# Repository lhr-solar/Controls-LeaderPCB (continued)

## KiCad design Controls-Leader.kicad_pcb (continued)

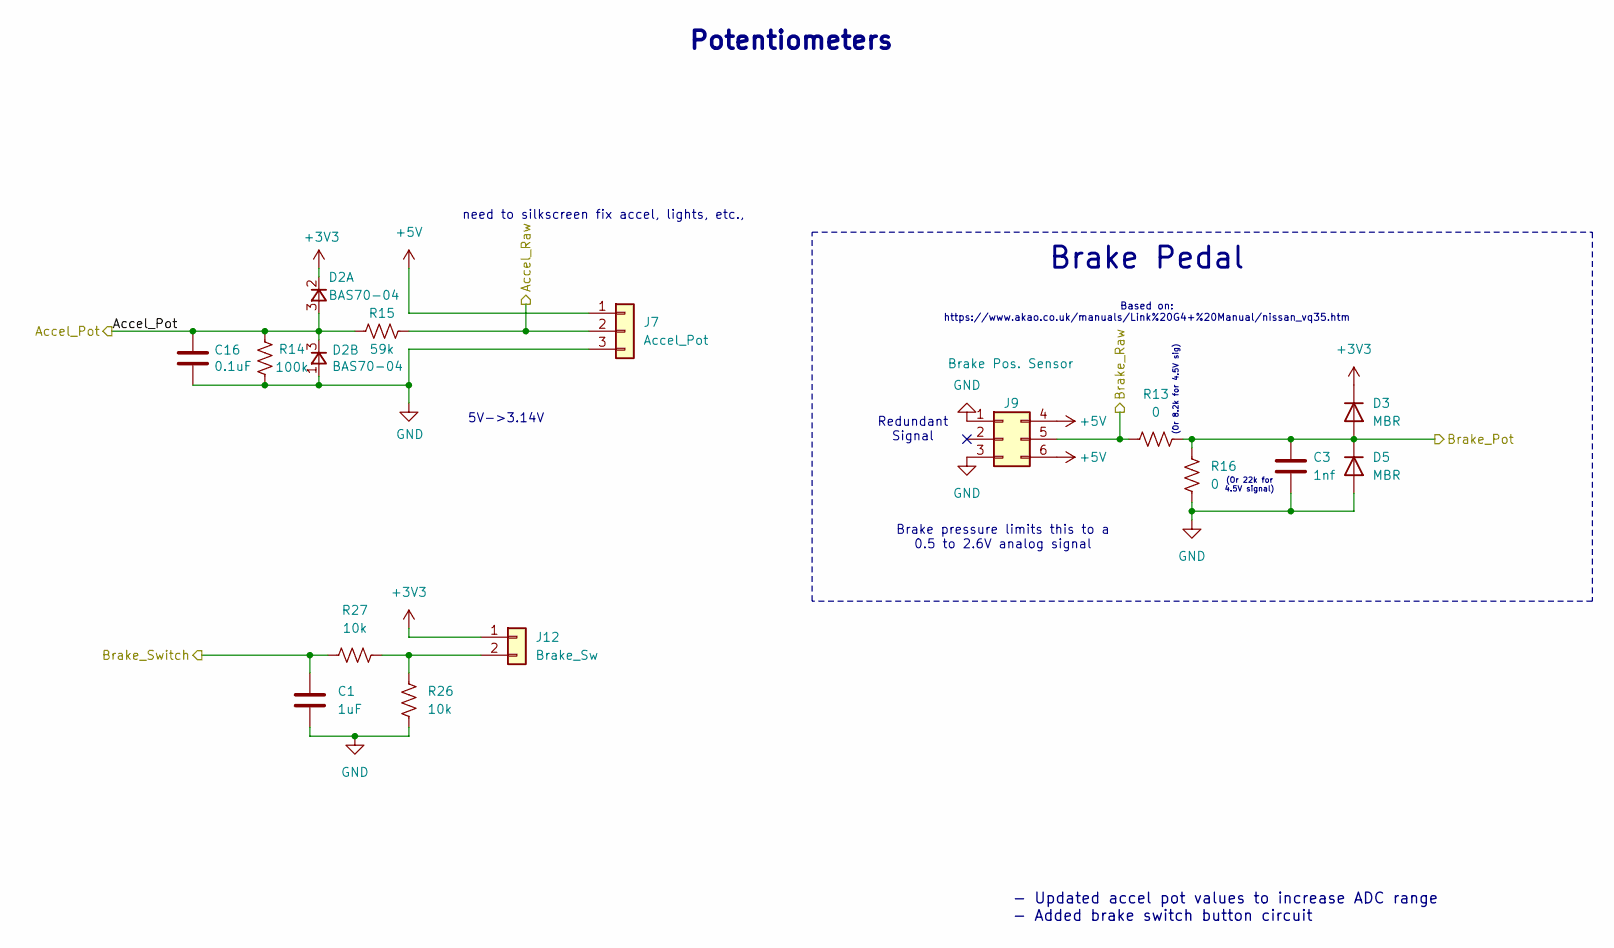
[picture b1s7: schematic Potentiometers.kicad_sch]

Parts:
C1: 1uF; C_0805_2012Metric; JLCPCB# C28323
C3: 1nf; C_0805_2012Metric; JLCPCB# C1791
C16: 0.1uF; C_0805_2012Metric; Mouser Part Number 80-C0805C104M5R
D2: BAS70-04; SOT-23; Mouser Part Number 652-CDSOT23-T24CAN
D3, D5: MBR; D_0805_2012Metric; JLCPCB# C23848
J7: Accel_Pot; Molex_Micro-Fit_3.0_43650-0315_1x03_P3.00mm_Vertical
J9: Brake Pos. Sensor; Molex_Micro-Fit_3.0_43045-0612_2x03_P3.00mm_Vertical
J12: Brake_Sw; Molex_Micro-Fit_3.0_43650-0215_1x02_P3.00mm_Vertical
R13, R16: 0; R_0805_2012Metric; JLCPCB# C17477
R14: 100k; R_0805_2012Metric; Mouser Part Number 71-CRCW0805100KFKEAC
R15: 59k; R_0805_2012Metric; Mouser Part Number 71-CRCW08054K99FKEAC
R26, R27: 10k; R_0805_2012Metric; Mouser Part Number 71-CRCW080510K0FKEAC

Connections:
+3V3: D2.2, D3.1 (K), D3.K, J12.1; also elsewhere on the board
+5V: J7.1, J9.4, J9.6; also elsewhere on the board
/Accel_Pot: C16.1, D2.3, R14.1, R15.2; also elsewhere on the board
/Accel_Raw: J7.2, R15.1; also elsewhere on the board
/Brake_Pot: C3.2, D3.2 (A), D3.A, D5.1 (K), D5.K, R13.1, R16.1; also elsewhere on the board
/Brake_Raw: J9.5, R13.2; also elsewhere on the board
/Brake_SW: C1.1, R27.1; also elsewhere on the board
GND: C1.2, C3.1, C16.2, D2.1, D5.2 (A), D5.A, J7.3, J9.1, J9.3, R14.2, R16.2, R26.2; also elsewhere on the board
unnamed: J12.2, R26.1, R27.2

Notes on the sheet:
(Or 22k for 4.5V signal)
Potentiometers
- Updated accel pot values to increase ADC range - Added brake switch button circuit
Redundant Signal
need to silkscreen fix accel, lights, etc.,
Brake pressure limits this to a 0.5 to 2.6V analog signal
5V->3.14V
(Or 8.2k for 4.5V sig)
Based on: https://www.akao.co.uk/manuals/Link%20G4+%20Manual/nissan_vq35.htm
Brake Pedal

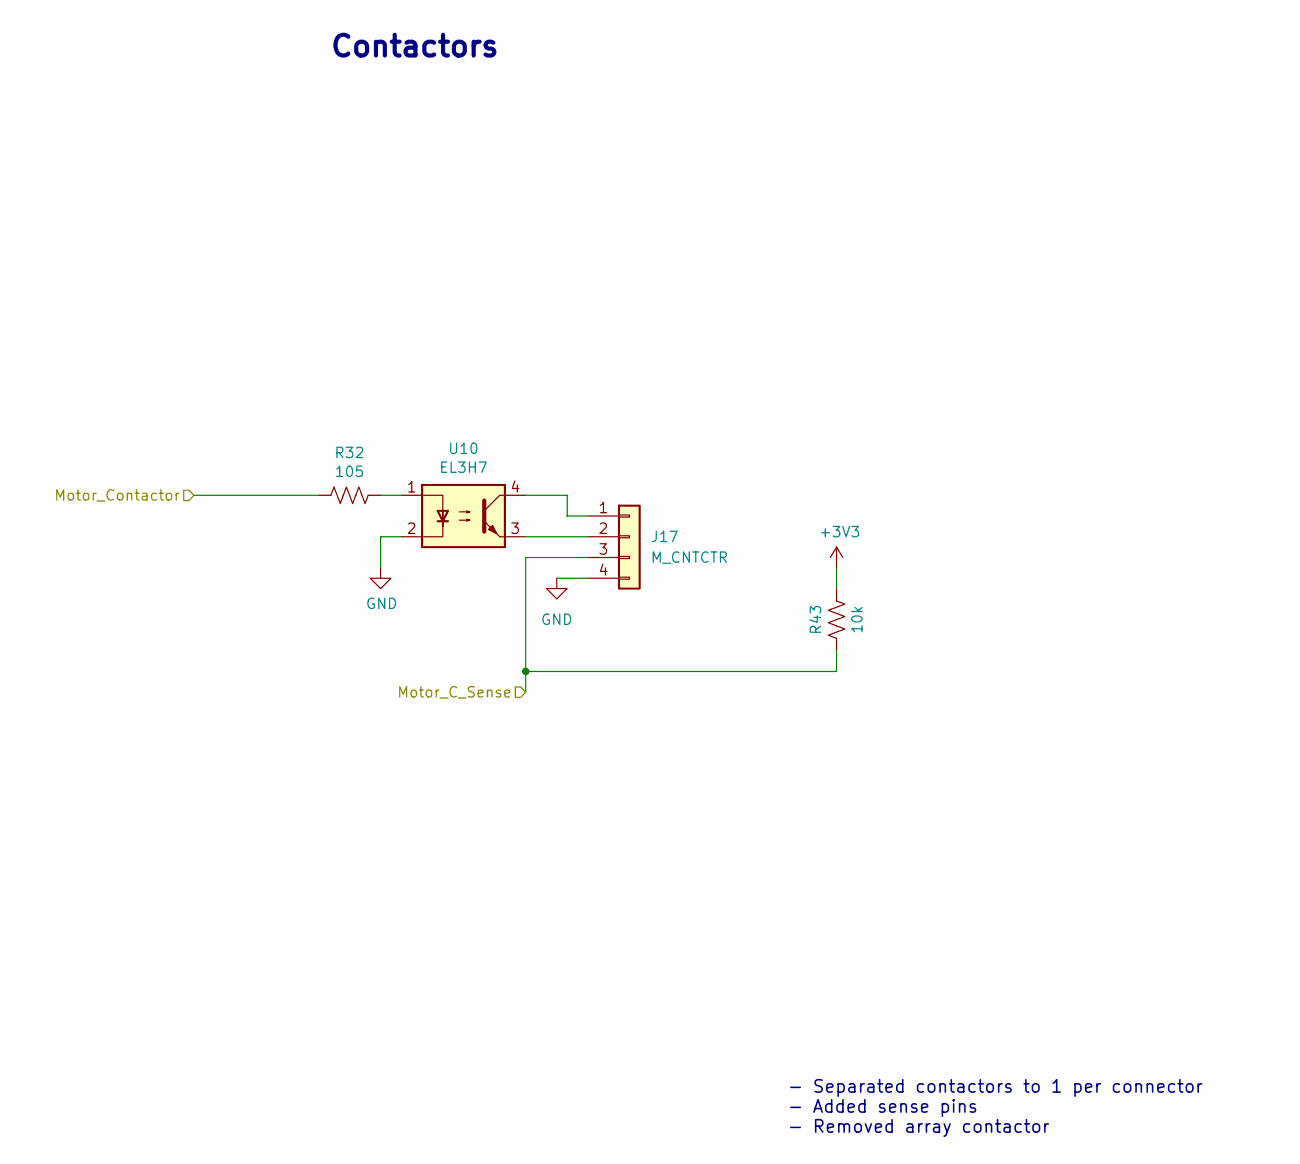
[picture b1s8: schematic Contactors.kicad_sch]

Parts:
J17: M_CNTCTR; Molex_Micro-Fit_3.0_43650-0415_1x04_P3.00mm_Vertical
R32: 105; R_0805_2012Metric; Mouser Part Number 71-CRCW0805105RFKEA
R43: 10k; R_0805_2012Metric; Mouser Part Number 71-CRCW080510K0FKEAC
U10: EL3H7; SSOP-4_4.4x2.6mm_P1.27mm; Mouser Part Number 638-EL3H7DTAVG

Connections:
+3V3: R43.1; also elsewhere on the board
/Motor_C_Sense: J17.3, R43.2; also elsewhere on the board
/Motor_Contactor: R32.2; also elsewhere on the board
GND: J17.4, U10.2; also elsewhere on the board
unnamed: J17.1, U10.4
unnamed: J17.2, U10.3
unnamed: R32.1, U10.1

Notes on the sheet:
Contactors
- Separated contactors to 1 per connector - Added sense pins - Removed array contactor

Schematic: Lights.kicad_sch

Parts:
BRAKELIGHT1: EXTERNAL_BRAKELIGHT; Molex_Micro-Fit_3.0_43650-0215_1x02_P3.00mm_Vertical; JLCPCB# C293740
LOGO4: UTSVT Logo; UTSVT_Logo_Symbol
L_BLINK_EXT1: EXTERNAL_LEFTBLINK; Molex_Micro-Fit_3.0_43650-0215_1x02_P3.00mm_Vertical; JLCPCB# C293740
Q1, Q3, Q4: IRLML0030; SOT-23; JLCPCB# C67272
R6, R12, R41: 510; R_0805_2012Metric; Mouser Part Number 71-CRCW0805510RFKEAC
R11, R45, R46: 100k; R_0805_2012Metric; Mouser Part Number 71-CRCW0805100KFKEAC
R_BLINK_EXT1: EXTERNAL_RIGHTBLINK; Molex_Micro-Fit_3.0_43650-0215_1x02_P3.00mm_Vertical; JLCPCB# C293740
TP7: RIGHT_BLINK; TestPoint_Keystone_5005-5009_Compact
TP8: LEFT_BLINK; TestPoint_Keystone_5005-5009_Compact
U3, U16, U20: EL3H7; SSOP-4_4.4x2.6mm_P1.27mm; Mouser Part Number 638-EL3H7DTAVG

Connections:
/Brake_Light: R6.1; also elsewhere on the board
/Left_Blink: R41.1, TP8.1; also elsewhere on the board
/Right_Blink: R12.1, TP7.1; also elsewhere on the board
GND: U3.2, U16.2, U20.2; also elsewhere on the board
GNDPWR: Q1.2 (S), Q3.2 (S), Q4.2 (S), R11.2, R45.2, R46.2; also elsewhere on the board
Lights_12V: BRAKELIGHT1.1, L_BLINK_EXT1.1, R_BLINK_EXT1.1, U3.4, U16.4, U20.4; also elsewhere on the board
unnamed: BRAKELIGHT1.2, Q1.3 (D)
unnamed: L_BLINK_EXT1.2, Q4.3 (D)
unnamed: Q1.1 (G), R11.1, U3.3
unnamed: Q3.3 (D), R_BLINK_EXT1.2
unnamed: Q3.1 (G), R45.1, U16.3
unnamed: Q4.1 (G), R46.1, U20.3
unnamed: R6.2, U3.1
unnamed: R12.2, U16.1
unnamed: R41.2, U20.1

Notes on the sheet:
Lights Drivers
- Replaced lights drivers/circuits - Replaced 555 timer with blinking gpio that passes through to drivers when dashboard Left/Right 3-pos switch is toggled - Intended to connect to breakout boards that split out the necessary number of lights

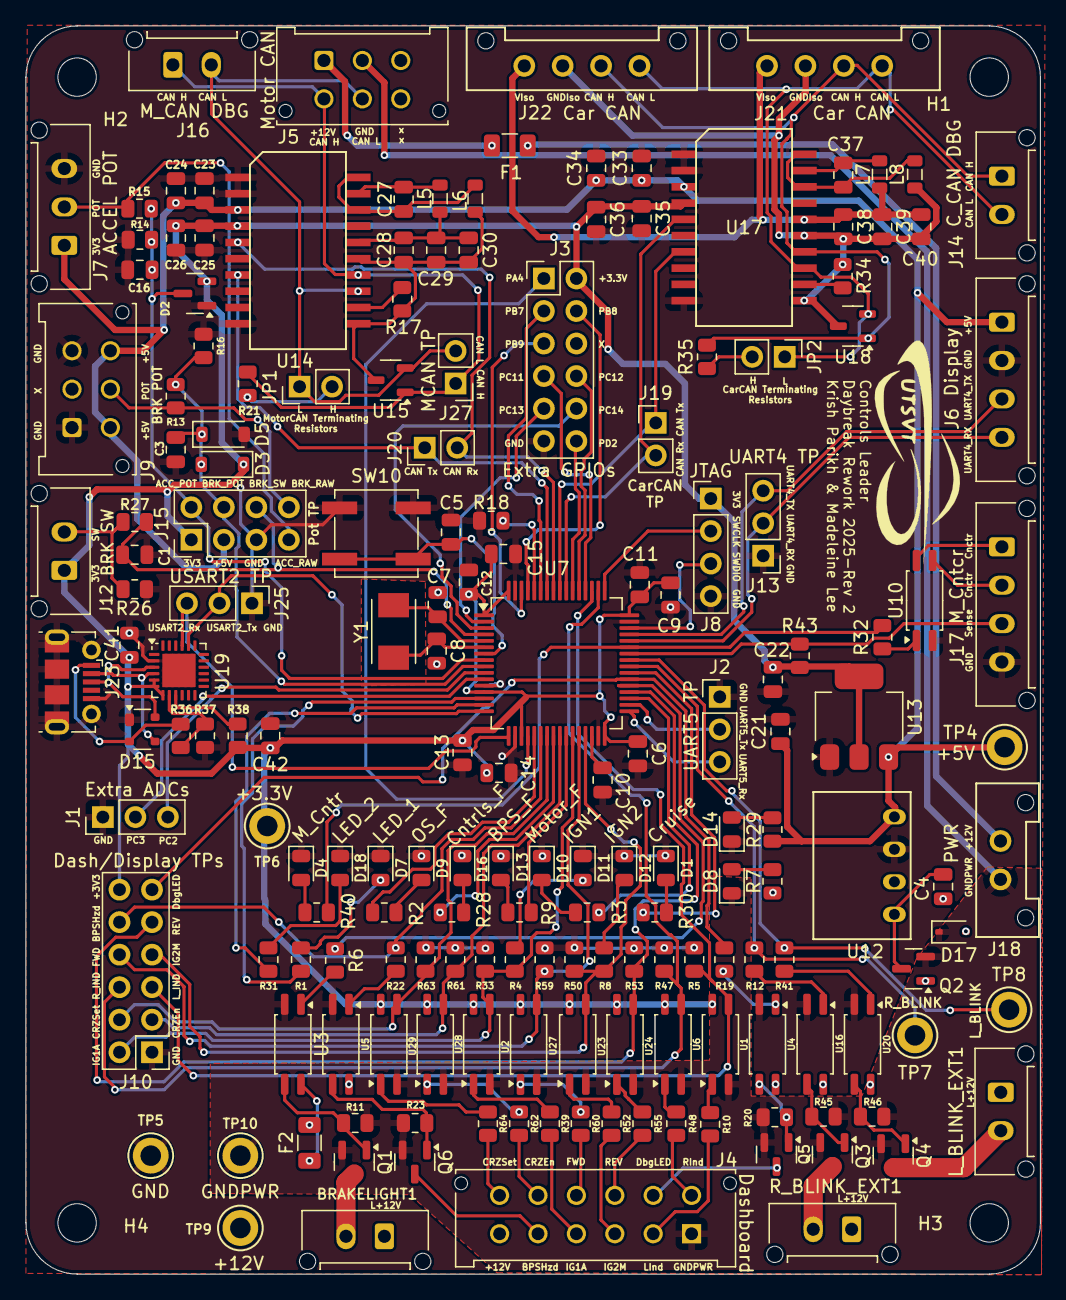
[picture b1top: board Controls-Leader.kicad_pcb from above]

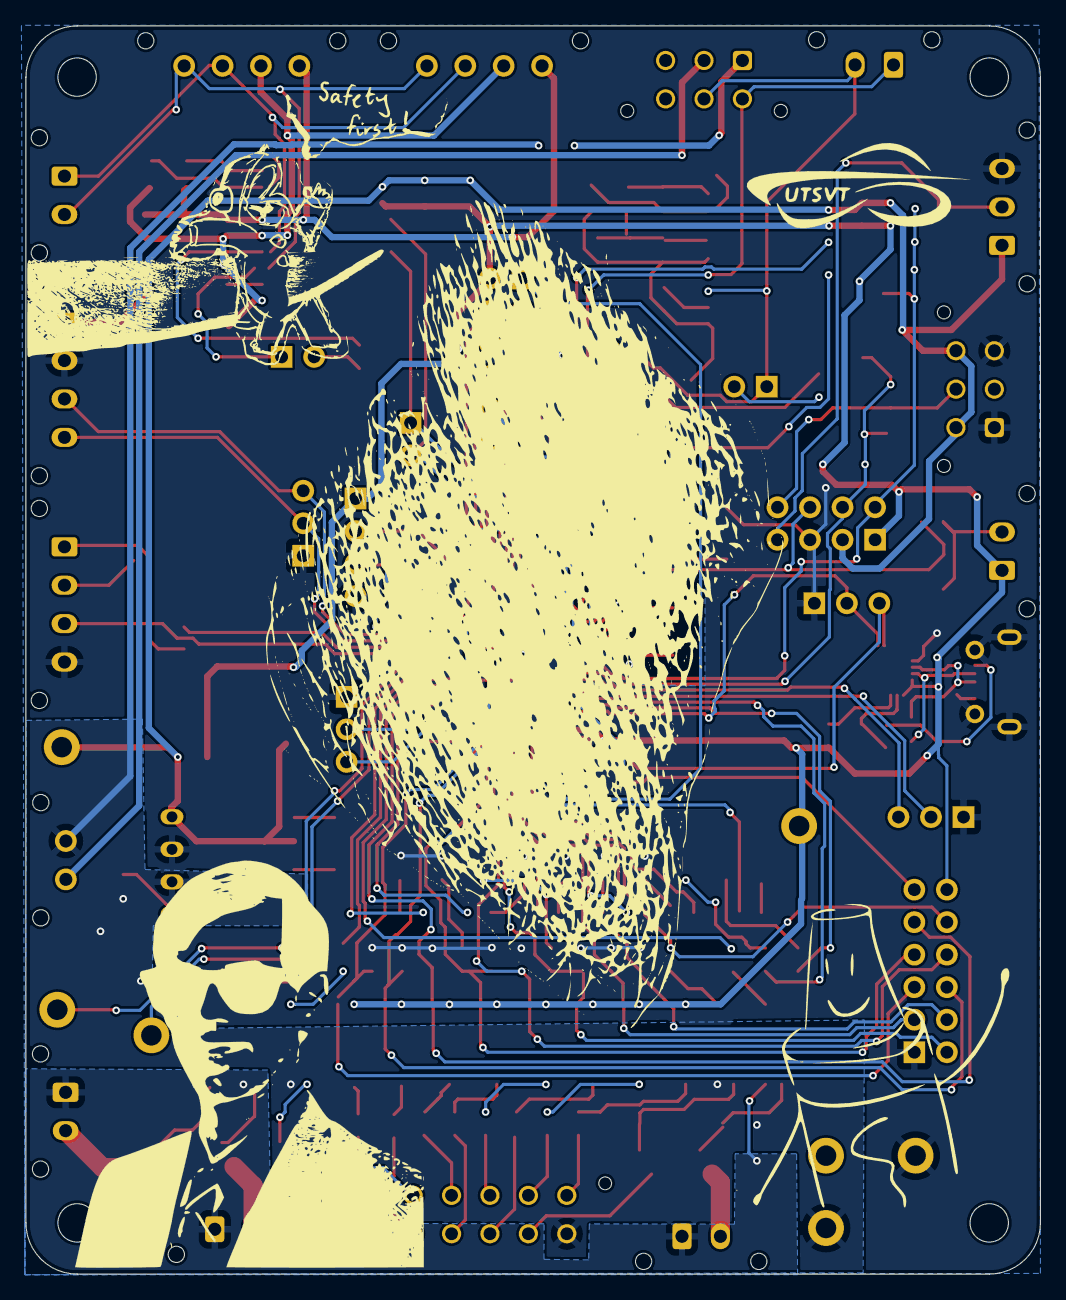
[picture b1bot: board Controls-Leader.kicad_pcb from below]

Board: 2 copper layers, 79.2 x 97.5 mm, 185 parts (2 on the bottom side), 131 nets.

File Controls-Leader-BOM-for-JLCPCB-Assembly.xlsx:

Comment | Designator | Footprint | JLCPCB#
1.8k | L5 | Inductor_SMD:L_0805_2012Metric | C394483
1.8k | L6 | Inductor_SMD:L_0805_2012Metric | C394483
1.8k | L7 | Inductor_SMD:L_0805_2012Metric | C394483
1.8k | L8 | Inductor_SMD:L_0805_2012Metric | C394483
CP2102N-A02-GQFN24 | U19 | Package_DFN_QFN:QFN-24-1EP_4x4mm_P0.5mm_EP2.6x2.6mm | C969151
698 | R1 | Resistor_SMD:R_0805_2012Metric | C101843
698 | R2 | Resistor_SMD:R_0805_2012Metric | C101843
698 | R3 | Resistor_SMD:R_0805_2012Metric | C101843
698 | R4 | Resistor_SMD:R_0805_2012Metric | C101843
698 | R8 | Resistor_SMD:R_0805_2012Metric | C101843
698 | R9 | Resistor_SMD:R_0805_2012Metric | C101843
698 | R28 | Resistor_SMD:R_0805_2012Metric | C101843
698 | R30 | Resistor_SMD:R_0805_2012Metric | C101843
698 | R31 | Resistor_SMD:R_0805_2012Metric | C101843
698 | R40 | Resistor_SMD:R_0805_2012Metric | C101843
Crystal | Y1 | Crystal:Crystal_SMD_TXC_7A-2Pin_5x3.2mm | C115962
100k | R11 | Resistor_SMD:R_0805_2012Metric | C149504
100k | R14 | Resistor_SMD:R_0805_2012Metric | C149504
100k | R20 | Resistor_SMD:R_0805_2012Metric | C149504
100k | R23 | Resistor_SMD:R_0805_2012Metric | C149504
100k | R45 | Resistor_SMD:R_0805_2012Metric | C149504
100k | R46 | Resistor_SMD:R_0805_2012Metric | C149504
10uF | C4 | Capacitor_SMD:C_0805_2012Metric | C15850
10uF | C21 | Capacitor_SMD:C_0805_2012Metric | C15850
10uF | C22 | Capacitor_SMD:C_0805_2012Metric | C15850
10uF | C23 | Capacitor_SMD:C_0805_2012Metric | C15850
10uF | C28 | Capacitor_SMD:C_0805_2012Metric | C15850
10uF | C33 | Capacitor_SMD:C_0805_2012Metric | C15850
10uF | C38 | Capacitor_SMD:C_0805_2012Metric | C15850
0.01uF | C26 | Capacitor_SMD:C_0805_2012Metric | C1710
0.01uF | C30 | Capacitor_SMD:C_0805_2012Metric | C1710
0.01uF | C36 | Capacitor_SMD:C_0805_2012Metric | C1710
0.01uF | C40 | Capacitor_SMD:C_0805_2012Metric | C1710
10k | R18 | Resistor_SMD:R_0805_2012Metric | C17414
10k | R26 | Resistor_SMD:R_0805_2012Metric | C17414
10k | R27 | Resistor_SMD:R_0805_2012Metric | C17414
10k | R43 | Resistor_SMD:R_0805_2012Metric | C17414
120 | R21 | Resistor_SMD:R_0805_2012Metric | C17437
105 | R32 | Resistor_SMD:R_0805_2012Metric | C17437
120 | R35 | Resistor_SMD:R_0805_2012Metric | C17437
0 | R13 | Resistor_SMD:R_0805_2012Metric | C17477
0 | R16 | Resistor_SMD:R_0805_2012Metric | C17477
0 | R17 | Resistor_SMD:R_0805_2012Metric | C17477
0 | R34 | Resistor_SMD:R_0805_2012Metric | C17477
1k | R38 | Resistor_SMD:R_0805_2012Metric | C17513
22.1k | R36 | Resistor_SMD:R_0805_2012Metric | C17560
2k | R10 | Resistor_SMD:R_0805_2012Metric | C17604
2k | R39 | Resistor_SMD:R_0805_2012Metric | C17604
2k | R48 | Resistor_SMD:R_0805_2012Metric | C17604
2k | R52 | Resistor_SMD:R_0805_2012Metric | C17604
2k | R55 | Resistor_SMD:R_0805_2012Metric | C17604
2k | R60 | Resistor_SMD:R_0805_2012Metric | C17604
2k | R62 | Resistor_SMD:R_0805_2012Metric | C17604
2k | R64 | Resistor_SMD:R_0805_2012Metric | C17604
47.5k | R37 | Resistor_SMD:R_0805_2012Metric | C17713
510 | R6 | Resistor_SMD:R_0805_2012Metric | C17734
510 | R12 | Resistor_SMD:R_0805_2012Metric | C17734
510 | R19 | Resistor_SMD:R_0805_2012Metric | C17734
510 | R22 | Resistor_SMD:R_0805_2012Metric | C17734
510 | R41 | Resistor_SMD:R_0805_2012Metric | C17734
59k | R15 | Resistor_SMD:R_0805_2012Metric | C17763
4.7uF | C10 | Capacitor_SMD:C_0805_2012Metric | C1779
4.7uF | C13 | Capacitor_SMD:C_0805_2012Metric | C1779
4.7uF | C41 | Capacitor_SMD:C_0805_2012Metric | C1779
1nf | C3 | Capacitor_SMD:C_0805_2012Metric | C1791
12pF | C7 | Capacitor_SMD:C_0805_2012Metric | C1792
12pF | C8 | Capacitor_SMD:C_0805_2012Metric | C1792
Fuse | F1 | Fuse:Fuse_1206_3216Metric | C206967
Fuse | F2 | Fuse:Fuse_1206_3216Metric | C206970
MBR | D3 | Diode_SMD:D_0805_2012Metric | C23848
MBR | D5 | Diode_SMD:D_0805_2012Metric | C23848
NCP1117-3.3_SOT223 | U13 | Package_TO_SOT_SMD:SOT-223-3_TabPin2 | C26537
4.9k | R5 | Resistor_SMD:R_0805_2012Metric | C27834
5.1k | R7 | Resistor_SMD:R_0805_2012Metric | C27834
4.9k | R33 | Resistor_SMD:R_0805_2012Metric | C27834
4.9k | R47 | Resistor_SMD:R_0805_2012Metric | C27834
4.9k | R50 | Resistor_SMD:R_0805_2012Metric | C27834
4.9k | R53 | Resistor_SMD:R_0805_2012Metric | C27834
4.9k | R59 | Resistor_SMD:R_0805_2012Metric | C27834
4.9k | R61 | Resistor_SMD:R_0805_2012Metric | C27834
4.9k | R63 | Resistor_SMD:R_0805_2012Metric | C27834
0.1uF | C5 | Capacitor_SMD:C_0805_2012Metric | C28233
0.1uF | C6 | Capacitor_SMD:C_0805_2012Metric | C28233
0.1uF | C9 | Capacitor_SMD:C_0805_2012Metric | C28233
0.1uF | C11 | Capacitor_SMD:C_0805_2012Metric | C28233
0.1uF | C12 | Capacitor_SMD:C_0805_2012Metric | C28233
0.1uF | C14 | Capacitor_SMD:C_0805_2012Metric | C28233
0.1uF | C16 | Capacitor_SMD:C_0805_2012Metric | C28233
0.1uF | C24 | Capacitor_SMD:C_0805_2012Metric | C28233
0.1uF | C25 | Capacitor_SMD:C_0805_2012Metric | C28233
0.1uF | C29 | Capacitor_SMD:C_0805_2012Metric | C28233
0.1uF | C34 | Capacitor_SMD:C_0805_2012Metric | C28233
0.1uF | C35 | Capacitor_SMD:C_0805_2012Metric | C28233
0.1uF | C39 | Capacitor_SMD:C_0805_2012Metric | C28233
0.1uF | C42 | Capacitor_SMD:C_0805_2012Metric | C28233
1uF | C1 | Capacitor_SMD:C_0805_2012Metric | C28323
1uF | C15 | Capacitor_SMD:C_0805_2012Metric | C28323
BAS70-04 | D2 | Package_TO_SOT_SMD:SOT-23 | C2959841
CDSOT23-T24CAN | U15 | Package_TO_SOT_SMD:SOT-23-3 | C2959841
CDSOT23-T24CAN | U18 | Package_TO_SOT_SMD:SOT-23-3 | C2959841
STM32F413RHTx | U7 | Package_QFP:LQFP-64_10x10mm_P0.5mm | C2969899
SP0503BAHTG | D15 | Package_TO_SOT_SMD:SOT-143 | C3040626
RESET | SW10 | Button_Switch_SMD:SW_SPST_B3SL-1002P | C318884
EL3H7 | U1 | Package_SO:SSOP-4_4.4x2.6mm_P1.27mm | C32565
EL3H7 | U2 | Package_SO:SSOP-4_4.4x2.6mm_P1.27mm | C32565
EL3H7 | U3 | Package_SO:SSOP-4_4.4x2.6mm_P1.27mm | C32565
EL3H7 | U4 | Package_SO:SSOP-4_4.4x2.6mm_P1.27mm | C32565
EL3H7 | U5 | Package_SO:SSOP-4_4.4x2.6mm_P1.27mm | C32565
EL3H7 | U6 | Package_SO:SSOP-4_4.4x2.6mm_P1.27mm | C32565
EL3H7 | U10 | Package_SO:SSOP-4_4.4x2.6mm_P1.27mm | C32565
EL3H7 | U16 | Package_SO:SSOP-4_4.4x2.6mm_P1.27mm | C32565
EL3H7 | U20 | Package_SO:SSOP-4_4.4x2.6mm_P1.27mm | C32565
EL3H7 | U23 | Package_SO:SSOP-4_4.4x2.6mm_P1.27mm | C32565
EL3H7 | U24 | Package_SO:SSOP-4_4.4x2.6mm_P1.27mm | C32565
EL3H7 | U27 | Package_SO:SSOP-4_4.4x2.6mm_P1.27mm | C32565
EL3H7 | U28 | Package_SO:SSOP-4_4.4x2.6mm_P1.27mm | C32565
EL3H7 | U29 | Package_SO:SSOP-4_4.4x2.6mm_P1.27mm | C32565
1.5k | R29 | Resistor_SMD:R_0805_2012Metric | C4310
IRLML0030 | Q1 | Package_TO_SOT_SMD:SOT-23 | C5364304
IRLML0030 | Q2 | Package_TO_SOT_SMD:SOT-23 | C5364304
IRLML0030 | Q3 | Package_TO_SOT_SMD:SOT-23 | C5364304
IRLML0030 | Q4 | Package_TO_SOT_SMD:SOT-23 | C5364304
IRLML0030 | Q5 | Package_TO_SOT_SMD:SOT-23 | C5364304
IRLML0030 | Q6 | Package_TO_SOT_SMD:SOT-23 | C5364304
Cruise Ind | D1 | LED_SMD:LED_0805_2012Metric | C5366381
M_CNCTR | D4 | LED_SMD:LED_0805_2012Metric | C5366381
STAT_LED_1 | D7 | LED_SMD:LED_0805_2012Metric | C5366381
PowerOn | D8 | LED_SMD:LED_0805_2012Metric | C5366381
OS Error | D9 | LED_SMD:LED_0805_2012Metric | C5366381
Motor Controller Fault | D10 | LED_SMD:LED_0805_2012Metric | C5366381
Ignition 1 | D11 | LED_SMD:LED_0805_2012Metric | C5366381
Ignition 2 | D12 | LED_SMD:LED_0805_2012Metric | C5366381
BPS Fault | D13 | LED_SMD:LED_0805_2012Metric | C5366381
PowerOn | D14 | LED_SMD:LED_0805_2012Metric | C5366381
Control Fault | D16 | LED_SMD:LED_0805_2012Metric | C5366381
STAT_LED_2 | D18 | LED_SMD:LED_0805_2012Metric | C5366381
0.22uF | C27 | Capacitor_SMD:C_0805_2012Metric | C5378
0.22uF | C37 | Capacitor_SMD:C_0805_2012Metric | C5378
ADM3055E | U14 | UTSVT_ICs:SOIC-20W_7.5x15.4mm_Pitch1.27mm | C658104
ADM3055E | U17 | UTSVT_ICs:SOIC-20W_7.5x15.4mm_Pitch1.27mm | C658104
RI3-1205S | U12 | UTSVT_ICs:RI3_DC_Converter | C7340248
SD12_SOD323 | D17 | Diode_SMD:D_SOD-323 | C85198
